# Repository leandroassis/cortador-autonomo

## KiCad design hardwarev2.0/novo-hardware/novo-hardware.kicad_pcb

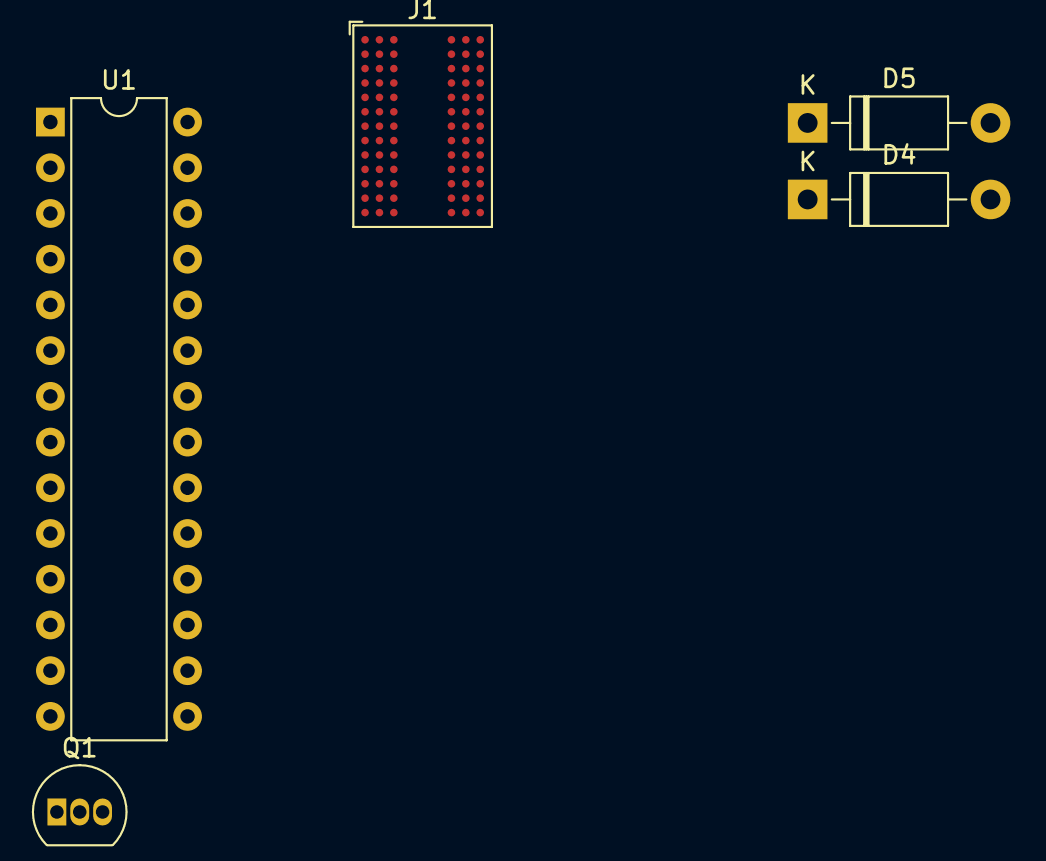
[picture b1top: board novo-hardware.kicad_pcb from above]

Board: 2 copper layers, 5 parts (0 on the bottom side), 3 nets, no tracks yet.

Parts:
D4, D5: 1N4001; D_DO-41_SOD81_P10.16mm_Horizontal
J1: Ext. Ultrassonic Sensor Conn.; FBGA-78_7.5x11mm_Layout2x3x13_P0.8mm
Q1: BC337; TO-92_Inline
U1: ATmega328P-P; DIP-28_W7.62mm

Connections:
12V_GND: U1.8 (GND), U1.22 (GND)
+5V: Q1.1 (C), U1.7 (VCC), U1.20 (AVCC), U1.21 (AREF)
unnamed: D4.1 (K), D5.1 (K)

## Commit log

2022-06-04 work-tree cleaned
2022-06-11 reinicializacao do repo
2022-06-11 inicialização e mapeamento OK
2022-06-24 Inicio das rotinas de TWI
